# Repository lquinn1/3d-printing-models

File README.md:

# 3D Printing Models

A collection of 3D printable models — source files, print-ready files, and print settings for each.

## Model Index

<!-- The section between the markers below is generated by scripts/build_index.py. Don't edit it by hand. -->
<!-- INDEX:START -->
**7 models**

### Electrical

| | Model | Description | Material | Status | Tags |
|---|-------|-------------|----------|--------|------|
|  | [Homeline Load Center Filler Plate](models/homeline-filler-plate/README.md) | Snap-in filler plates (1- and 2-pole) for empty breaker openings in a Square D Homeline panel cover. Inspired by the HOMFPCP. | PLA (tested); ABS / ASA / PC recommended | Working | `electrical` `load-center` `breaker-panel` `filler-plate` `square-d` `homeline` `snap-fit` |

### Kitchen & BBQ

| | Model | Description | Material | Status | Tags |
|---|-------|-------------|----------|--------|------|
|  | [BBQ Probe Spool Stand](models/bbq-probe-spool-stand/README.md) | Stand for rotary BBQ probe spools, with front clips for the probe tips and a storage box with two pockets (V3). | ABS | Working | `bbq` `thermometer` `probe` `organizer` `storage` `inkbird` `alpha-grillers` |

### Lighting

| | Model | Description | Material | Status | Tags |
|---|-------|-------------|----------|--------|------|
|  | [Dragon Egg Nightlight](models/dragon-egg-nightlight/README.md) | Scaled dragon-egg lamp shade with an engraved base and a press-fit E26 socket deck, about 264 mm tall assembled. | PLA egg / ABS base and deck | Working | `nightlight` `lamp` `nursery` `dragon-egg` `e26` |

### Multiboard

| | Model | Description | Material | Status | Tags |
|---|-------|-------------|----------|--------|------|
|  | [Multiboard LED Light Bar](models/multiboard-led-light-bar/README.md) | One wedge bracket that holds an 18 x 8.5 mm LED channel on a Multiboard, aimed down the wall at 30°. The channel passes through, so use as many as you need, anywhere along the bar. | PLA (tested), PETG or ABS | Working | `multiboard` `led` `light-bar` `wall-wash` `push-fit` `honeycomb` |

### Organization

| | Model | Description | Material | Status | Tags |
|---|-------|-------------|----------|--------|------|
|  | [Example Cable Clip](models/example-cable-clip/README.md) | Placeholder model showing the README format. Delete once you add real models. | PETG | Example | `example` `cable-management` |
|  | [Remote Control Wall Holder](models/remote-wall-holder/README.md) | Slide-in wall cradle for a slim 151 x 38 x 13 mm LED-light remote. Screws to the wall; the remote lifts straight up and out. | PLA or PETG | Working | `remote` `wall-mount` `holder` `slide-in` `led-remote` `drywall` |

### Storage

| | Model | Description | Material | Status | Tags |
|---|-------|-------------|----------|--------|------|
|  | [Filament Dry Cabinet](models/filament-dry-cabinet/README.md) | Modular, stackable, heated and desiccant-dried 12-spool cabinet (one per material). ESPHome control, SK6812 lighting, closable PTFE ports and Spoolman slot IDs. Under 20 in deep and tall. | ABS / ASA | Design | `filament` `dry-box` `dehumidifier` `esphome` `esp32` `sk6812` `spoolman` `openprinttag` `nfc` `dowel` `modular` `stackable` `ptfe` |
<!-- INDEX:END -->

## Repository Layout

```
models/
  _template/            # copy this to start a new model
  <model-name>/
    README.md           # description, print settings, BOM, notes
    files/              # STL, 3MF, STEP, F3D, SCAD, etc.
    images/             # preview.png and build photos
scripts/
  build_index.py        # regenerates the index above
```

## Adding a Model

1. Copy `models/_template` to `models/<model-name>` (lowercase, hyphens, e.g. `spool-holder`).
2. Fill in the front matter at the top of the new `README.md` (`title`, `category`, `summary`, `material`, `status`, `tags`, and optionally `thumbnail`: the picture shown in the index; without it the first image in the README is used) and the rest of the page.
3. Put printable/source files in `files/` and a `preview.png` in `images/`.
4. Commit and push. The GitHub Action rebuilds the index automatically. To rebuild locally instead, run:

   ```
   python3 scripts/build_index.py
   ```

**Status values** (suggested): `Draft`, `Testing`, `Working`, `Final`, `Deprecated`.

## License

Unless a model folder has its own `LICENSE.md`:

- **Models and docs** (STL/STEP/3MF, READMEs, drawings, photos): [CC BY-NC-SA 4.0](https://creativecommons.org/licenses/by-nc-sa/4.0/). Free to print, modify and share with credit, **no commercial use**, and remixes keep the same license.
- **Code** (scripts in each model's `source/` or `cad/` folder, and `scripts/`): **MIT**.

Models with their own license:
- **BBQ Probe Spool Stand:** CC BY-SA 4.0, as required by the original it remixes (commercial use allowed with credit).
- **Filament Dry Cabinet:** same split as the default, with its vendor reference files excluded.

See [`LICENSE`](LICENSE).

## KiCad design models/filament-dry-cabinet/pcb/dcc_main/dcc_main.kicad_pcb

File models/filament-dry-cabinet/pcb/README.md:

# Cabinet electronics: two PCBs

Replaces the Perma-Proto protoboard. Everything is through-hole, so it can all be hand-soldered.

| Board | Size | Where | What's on it |
|---|---|---|---|
| **DCC-MAIN** (`dcc_main/`) | 170 × 60 mm, 2 layers, **2 oz copper** | Rear pod, on `carrier_main` (4 × M3, 160 × 50 mm: on the carrier's 10 mm grid) | ESP32-S3-DevKitC-1 in sockets, 10 A blade fuse, heater relay (G5LE) + MOSFET, fan driver with tach input and its own 0.5 A PTC fuse, 5 V distribution with a 3 A PTC for the LEDs, I²C pull-ups, NTC divider, door-reed input, ribbon header |
| **DCC-FRONT** (`dcc_front/`) | 80 × 44 mm, 2 layers, 1 oz | Header bay back plate, between the display and the encoder (x 335–415), over the cable slot | Ribbon header, display / NFC / encoder headers, 74AHCT125 LED level shifter with 330 Ω and 1000 µF at the strip, encoder pull-ups and filters, door-reed terminal |

Schematic: [`schematic.pdf`](schematic.pdf) (also [`../images/pcb_schematic.png`](../images/pcb_schematic.png)).

Wiring between the boards and everything else: [`../wiring/wire_list.csv`](../wiring/wire_list.csv) and DESIGN.md §19.

## Ordering

Upload `dcc_main/dcc_main_gerbers.zip` and `dcc_front/dcc_front_gerbers.zip` as they are (Gerber + Excellon, KiCad names). Use the house defaults (1.6 mm FR-4, HASL or ENIG, any colour), but **order the controller with 2 oz outer copper**: the heater's 6.3 A runs through it on 2 mm tracks and both ground pours. Parts per board: `dcc_*_bom.csv`. They're also in the cabinet BOM.

## How the heater is switched

`+24V → F1 (10 A) → K1 relay contact → J2 heater (with the 102 °C TCO in its lead) → Q1 MOSFET → GND`

- **Q1 (GPIO45)** does the PWM (about a 5 s period in ESPHome `slow_pwm`).
- **K1** is the safety switch. Its coil is fed through the **KSD301 (J3)**, so at 85 °C the thermostat drops the relay whatever the firmware does. Q2 (GPIO46) lets the firmware drop it too, for the interlocks.
- **GPIO45 and GPIO46 are ESP32-S3 boot-strap pins.** Each has a 10 kΩ pull-down (R4, R2), which keeps it low at reset, as the chip needs. It also means the heater and relay are off while the board boots.

## Pin map and ribbon

The ESP32 pin map and the 26-way ribbon pinout are on the last two pages of the schematic, and in [`circuit.py`](circuit.py), which is the source for both boards.

- **Not used:** GPIO35–37 (octal PSRAM on the N16R8 module), GPIO19/20 (USB), GPIO43/44 (log UART), GPIO0 (BOOT), GPIO38/48 (the DevKit's RGB LED).
- **Fan PWM is inverted.** Q3 is an open collector, so set `inverted: true` on the ESPHome output. At boot Q3 is off, so the fan runs at full speed until the firmware takes over, which is the safe way round.
- **Ribbon:** in the flat cable, SCK, MOSI, MISO and the LED data line each sit next to a ground wire. Keep SPI at 10 MHz or less.

## DevKit header spacing

Espressif's drawing puts the two pin rows 22.86 mm apart, but some boards measure 25.4 mm. U1B has a **second row of holes 2.54 mm further out**, wired in parallel. Measure your board and solder the J3 socket into whichever row fits; leave the other row empty.

## Checks (run on every build)

- **DRC: 0 errors, 0 unconnected pads** on both boards. Reports: `dcc_*_drc.txt`. The only warnings left are silkscreen labels touching outlines.
- **Every pad's net matches `circuit.py`.**
- **Track widths:** heater and 24 V nets are 2.0 mm, 5 V nets 1.0 mm, signals 0.4 mm. Clearance is 0.2 mm (0.3 mm on the 24 V nets).
- **Copper keep-outs:** none under the DevKit's antenna, and none within 0.8 mm of the board edge.
- **Schematic cross-check:** all 43 parts drawn in the schematic are on the boards with the same values, and vice versa.

## Rebuild

```
python3 pcb/build.py        # place, autoroute, pour ground, DRC, Gerbers + drill, per-board BOM
python3 pcb/schematic.py    # schematic.pdf and images/pcb_schematic.png
```

You need KiCad 7 (`kicad-cli` and the `pcbnew` Python module), Java, `freerouting.jar` v1.9 (set `FREEROUTING` to its path), and `xvfb-run`. Placement lives in `circuit.py`: move a part there, rerun, and the router lays the tracks again. The `.kicad_pcb` files open in KiCad 7 or later if you'd rather edit the layout by hand.

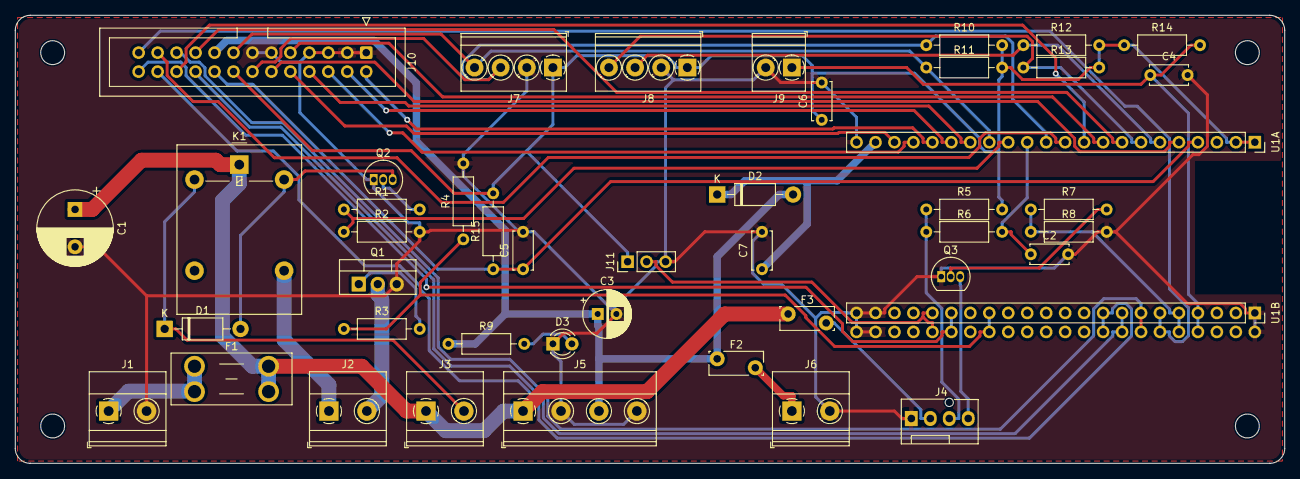
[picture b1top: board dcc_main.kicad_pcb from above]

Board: 2 copper layers, 170.0 x 60.0 mm, 49 parts (0 on the bottom side), 44 nets.

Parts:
C1: 100uF 35V; CP_Radial_D10.0mm_P5.00mm
C2: 10nF; C_Disc_D5.0mm_W2.5mm_P5.00mm
C3: 100uF 10V; CP_Radial_D6.3mm_P2.50mm
C4, C5, C6, C7: 100nF; C_Disc_D5.0mm_W2.5mm_P5.00mm
D1: 1N4007; D_DO-41_SOD81_P10.16mm_Horizontal
D2: 1N5819; D_DO-41_SOD81_P10.16mm_Horizontal
D3: PWR; LED_D3.0mm
F1: 10 A mini blade; Fuseholder_Blade_Mini_Keystone_3568
F2: 3A PTC; Fuse_Bourns_MF-RG300
F3: 0.5A PTC; Fuse_Bourns_MF-RG300
H1, H2, H3, H4: MountingHole_3.2mm_M3
J1: 24 V IN; TerminalBlock_Phoenix_MKDS-1,5-2-5.08_1x02_P5.08mm_Horizont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
J2: HEATER; TerminalBlock_Phoenix_MKDS-1,5-2-5.08_1x02_P5.08mm_Horizont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
J3: KSD301; TerminalBlock_Phoenix_MKDS-1,5-2-5.08_1x02_P5.08mm_Horizont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
J4: FAN 24V PWM; FanPinHeader_1x04_P2.54mm_Vertical
J5: BUCK 24V/5V; TerminalBlock_Phoenix_MKDS-1,5-4-5.08_1x04_P5.08mm_Horizont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
J6: LED 5V OUT; TerminalBlock_Phoenix_MKDS-1,5-2-5.08_1x02_P5.08mm_Horizont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
J7: SHT45 CHAMBER; TerminalBlock_Phoenix_PT-1,5-4-3.5-H_1x04_P3.50mm_Horizontal
J8: SHT40 PLENUM; TerminalBlock_Phoenix_PT-1,5-4-3.5-H_1x04_P3.50mm_Horizontal
J9: NTC; TerminalBlock_Phoenix_PT-1,5-2-3.5-H_1x02_P3.50mm_Horizontal
J10: FRONT 2x13; IDC-Header_2x13_P2.54mm_Vertical
J11: SPARE IO21; PinHeader_1x03_P2.54mm_Vertical
K1: G5LE-1A4 DC24; Relay_SPDT_Omron-G5LE-1
Q1: IRLB3034; TO-220-3_Vertical
Q2, Q3: 2N3904; TO-92_Inline
R1, R7: 4k7; R_Axial_DIN0207_L6.3mm_D2.5mm_P10.16mm_Horizontal
R2, R4, R5, R8, R15: 10k; R_Axial_DIN0207_L6.3mm_D2.5mm_P10.16mm_Horizontal
R3: 100R; R_Axial_DIN0207_L6.3mm_D2.5mm_P10.16mm_Horizontal
R6, R9: 1k; R_Axial_DIN0207_L6.3mm_D2.5mm_P10.16mm_Horizontal
R10, R11, R12, R13: 2k2; R_Axial_DIN0207_L6.3mm_D2.5mm_P10.16mm_Horizontal
R14: 10k 1%; R_Axial_DIN0207_L6.3mm_D2.5mm_P10.16mm_Horizontal
U1A: ESP32 J1; PinSocket_1x22_P2.54mm_Vertical
U1B: ESP32 J3; PinSocket_1x22_P2.54mm_TwinRow

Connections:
+3V3: C6.1, J7.1, J8.1, J10.16, J11.1, R5.2, R10.2, R11.2, R12.2, R13.2, R14.1, R15.2, U1A.1, U1A.2
+5V: C3.1, D2.2, F2.1, J5.3, J10.17, R9.1
+24V: C1.1, F1.2, F3.1, J3.1, J5.1, K1.1
+24V_IN: F1.1, J1.1
COIL_LO: D1.2, K1.5, Q2.3
CTP_INT: J10.21, U1B.7
ENC_A: J10.24, U1B.9
ENC_B: J10.25, U1B.6
ENC_SW: J10.26, U1B.17
ESP_5V: C7.1, D2.1, U1A.21
FAN_24V: F3.2, J4.2
FAN_OC: J4.4, Q3.3
FAN_PWM: R7.1, R8.1, U1B.5
FAN_TACH: C2.1, R6.2, U1A.13
FRONT_RST: J10.20, U1B.8
GND: C1.2, C2.2, C3.2, C4.2, C5.2, C6.2, C7.2, D3.1, J1.2, J4.1, J5.2, J5.4, J6.2, J7.2, J8.2, J9.2, J10.1, J10.3, J10.5, J10.7, J10.11, J10.13, J11.3, Q1.3, Q2.1, Q3.1, R2.2, R4.2, R8.2, U1A.22, U1B.1, U1B.21, U1B.22
HTR_N: J2.2, Q1.2
HTR_P: J2.1, K1.4
HTR_PWM: R3.1, R4.1, U1B.15
LED_5V: F2.2, J6.1
LED_A: D3.2, R9.2
LED_DIN: J10.12, U1A.5
MISO: J10.6, U1A.19
MOSI: J10.4, U1A.17
NFC_BUSY: J10.22, U1A.10
NFC_NSS: J10.9, U1A.9
NFC_RST: J10.23, U1A.11
NTC: C4.1, J9.1, R14.2, U1B.4
Q1_G: Q1.1, R3.2
Q2_B: Q2.2, R1.2
Q3_B: Q3.2, R7.2
REED: C5.1, J10.18, R15.1, U1A.4
RELAY_EN: R1.1, R2.1, U1A.14
SCK: J10.2, U1A.18
SCL_A: J7.4, J10.15, R11.1, U1A.15
SCL_B: J8.4, R13.1, U1A.7
SDA_A: J7.3, J10.14, R10.1, U1A.12
SDA_B: J8.3, R12.1, U1A.6
SPARE_IO21: J11.2, U1B.18
TACH_RAW: J4.3, R5.1, R6.1
TFT_BL: J10.19, U1A.8
TFT_CS: J10.8, U1A.16
TFT_DC: J10.10, U1A.20
TSTAT_OUT: D1.1, J3.2, K1.2

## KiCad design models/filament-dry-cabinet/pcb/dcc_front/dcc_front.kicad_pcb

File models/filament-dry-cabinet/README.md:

---
title: Filament Dry Cabinet
category: Storage
status: Design
material: ABS / ASA
printer: Voron 2.4 R2 350
tags: [filament, dry-box, dehumidifier, esphome, esp32, sk6812, spoolman, openprinttag, nfc, dowel, modular, stackable, ptfe]
thumbnail: images/thumbnail.jpg
summary: Modular, stackable, heated and desiccant-dried 12-spool cabinet (one per material). ESPHome control, SK6812 lighting, closable PTFE ports and Spoolman slot IDs. Under 20 in deep and tall.
---

# Filament Dry Cabinet

A modular cabinet that stores **12 × 1 kg spools** and keeps them dry. A low-voltage **PTC heater** circulates warm air through **pull-out silica gel cartridges**. An **ESP32 running ESPHome** controls it, with a local display and knob for setpoints, and integrates with Home Assistant. **SK6812** lighting can highlight individual slots. Each spool position has an ID (`PETG-F3`, for example) for Spoolman's Location field. You'll build **one cabinet per material**. It plugs in through an **IEC C14 fused inlet** (120 V). At **19.4 in deep and 19.4 in tall**, it fits standard 20 in shelves. Cabinets **stack**, and **closable PTFE ports** on the top and back can feed a printer straight from any slot.

**Status: CAD, PCBs and firmware done; ready for the test build.** The shell (§13), front frame and header (§14), door (§15), rear pod (§16), interior drying unit (§17) and fit-test coupons (§12); two custom PCBs (§18), wiring (§19) and the ESPHome firmware (`firmware/`). The as-built parts list is in **[BOM.md](BOM.md)** (about $1,018 for one cabinet). The PN5180 NFC component is next. See **[DESIGN.md](DESIGN.md)** for the full spec.

*The top picture is a Blender/Cycles render of the CAD (`source/render/photo/`); the printer in it is a simplified stand-in. The others are rendered straight from the CAD (`cad/render_hero.py`).*

## At a Glance

| | |
|---|---|
| Capacity | 12 spools: two rows of 6, with the back row raised 120 mm |
| Size | 531 W × 442 D (492 with rear control pod) × 494 H mm (20.9 × 17.4 / 19.4 × 19.4 in) |
| Shelves | 1 in poplar dowel rods (same in every cabinet) in printed cradles, with printed index collars every 80 mm |
| Shell | Printed ABS/ASA tile panels (≤ 330 mm) with 1/2 in XPS foam, and a twin-pane polycarbonate door |
| PTFE ports | 12 on top (one per slot) + 12 on the back. Each one takes a PTFE pass-through module (PC4-M10) or a sealed blank plug. |
| Stacking | Feet nest into pockets in the cabinet below, with optional side links. Stacks of 2–3. |
| Drying | 24 V PTC heater, 150 W in every cabinet with PID (autotune), + PWM fan + about 700 g of silica gel |
| Control | ESP32-S3, SHT45/SHT40, 3.5 in IPS capacitive touchscreen TFT, 480 × 320 (shows the label; touch firmware later) + encoder, ESPHome |
| NFC | **PN5180 tap pad** in the header for **OpenPrintTag** (ISO 15693) and NTAG tags. Tap a spool and pick a slot, and Spoolman's Location updates. |
| Power | 120 V IEC C14 fused and switched inlet → Mean Well 24 V PSU in a rear pod outside the chamber |
| Door | Twin-pane polycarbonate, soft neoprene seal, flush lift-bar handle that is also a draw-in latch |
| Safety | Hardware thermal cutouts (85 °C auto-reset on a heater relay + 102 °C fuse) and firmware interlocks |

## Files

| File | Description |
|------|-------------|
| [`firmware/`](firmware/README.md) | ESPHome firmware for one cabinet (`dry-cabinet.yaml`), with flashing steps, first power-up checks and how the control works |
| [`pcb/`](pcb/README.md) | Electronics: two KiCad PCBs (controller + front breakout) built from `circuit.py`, with Gerbers, schematic and per-board BOMs |
| [`cad/`](cad/) | Parametric CAD: `params.py` (all dimensions), `coupons.py` (fit-test parts), `tiles.py` (20 shell tiles, feet, cradles), `front.py` (frame, header, LED rails), `door.py` (door, hinges, lift-bar latch, tag), `render_latch.py` (latch renders and animation), `latch_coupon.py` (latch fit-test coupon), `pod.py` (rear pod), `interior.py` (desiccant, plenum, heater and floor ducts, sensor housings), `verify*.py` (assembly and swing checks), `preview.py` / `render_tiles.py` (images); STLs in `cad/stl/` |
| [`DESIGN.md`](DESIGN.md) | Full design spec: requirements, layout options, construction, drying, electronics, ESPHome entities, Spoolman scheme, parts list, open questions |
| [`BOM.md`](BOM.md), [`BOM.csv`](BOM.csv) | As-built bill of materials: links, prices, quantities, where each part is used, status and test results. Generated from `bom/bom_source.csv` by `bom/build_bom.py` |
| [`QA_REVIEW.md`](QA_REVIEW.md) | Design and CAD QA review: what was fixed, and prioritised recommendations |
| [`images/render_front.jpg`](images/render_front.jpg), [`render_stack.jpg`](images/render_stack.jpg), [`render_rear.jpg`](images/render_rear.jpg) | Concept renders (front, stacked pair, rear) |
| [`images/wiring.png`](images/wiring.png) | Electrical block diagram |
| [`source/layout.py`](source/layout.py) | Layout calculator. Change the spool and rod sizes or the offset and rerun it. |
| [`source/draw.py`](source/draw.py), [`source/wiring.py`](source/wiring.py) | Scripts that draw the layout and wiring figures |
| [`source/render/`](source/render/) | The software renderer (`scene.py`) used by every `cad/render_*.py`. The three presentation views (front, rear, stack) come from `cad/render_hero.py`, built from the real CAD parts |

## License

- **Design files and docs** (STL/STEP, DESIGN.md, drawings, renders): [CC BY-NC-SA 4.0](https://creativecommons.org/licenses/by-nc-sa/4.0/). Free to build, modify and share with credit, but **no commercial use**, and remixes keep the same license.
- **Code** (Python in `cad/`, `source/` and `bom/`, and the ESPHome YAML and components when they're added): **MIT**.
- The display vendor's drawing and pinout in `docs/`, and `images/concept.jpg`, aren't covered.

See [`LICENSE.md`](LICENSE.md).

## Revision History

- **v0.25** (2026-11-25): **fit-test round 2.** `tile_joint_b` confirmed (0.05 mm flank gap). Port thread clearance **0.35 mm** (was 0.25), tested with **wall order inner/outer** (now in the print settings): the seven socket tiles, plug, PTFE module and gland regenerated. O-ring groove ID **23.0** (was 22.6) so the ring holds on better, plus a new `oring_groove_coupon` (22.6 / 23.0 / 23.4) to confirm it.
- **v0.24** (2026-11-25): **bottom LED strip.** Two new printed rails (`led_rail_bottom_left/right`) on the floor behind the door sill, flush with it, carry 23 more SK6812 LEDs aimed up and back at the spools, with a gap at slot 3 for the floor duct. One data chain of 51 LEDs: the top strip (data in at the right) feeds the bottom one through a wire down the front-left corner (W26, W27). Firmware: per-slot lights cover both strips, plus a **2.0 A LED current cap** so the 3 A 5 V supply is never overloaded. Inserts in the bottom rail; wiring, BOM quantities and renders updated (total unchanged, about $1,018).
- **v0.23.1** (2026-11-25): **photoreal render** of two cabinets on a wire shelf next to a Voron 2.4-style printer ([`images/render_photo_shelf.jpg`](images/render_photo_shelf.jpg)), Blender/Cycles from the CAD (`source/render/photo/`).
- **v0.23** (2026-11-25): **5 V supply is now a Mean Well SD-15B-5** ($14.80, 18–36 V in, 5 V 3 A, protected) in place of the $39.95 Pololu D36V50F5; it sits on `carrier_left` between printed corner stops (checked against the cover, PSU and glands). 5 V budget worked out: about 2 A worst real case. **Controller is now the ESP32-S3-DevKitC-1-N16R8** (16 MB flash; same pinout), firmware set to 16 MB and recompiled. Wiring list, schematic and pod render updated. About $1,018.
- **v0.22** (2026-11-25): **1 in poplar dowels replace the PVC rods** (Madison Mill 436580, two 48 in dowels per cabinet). One rod type for every plastic, and about 0.3 mm sag loaded against 2 mm or more for PVC at 50 °C, so the CPVC line for hot cabinets is gone. Rod cradles and collars resized for 25.4 mm (collar grip raised for undersize dowels); the cabinet size is unchanged. New prep steps: pre-dry, seal and measure the dowels (§4.3). BOM about $1,043.
- **v0.21** (2026-11-25): the NFC tap zone is now a **64 × 46 mm rectangle with a phone-and-waves icon and TAP HERE**, and the encoder gets a **printed orange knob** (`encoder_knob`, D-bore for the 6 mm shaft) in place of the aluminium one. Renders and the front layout drawing updated. About $1,026.
- **v0.20** (2026-11-25): **orange accents.** New `tft_bezel` (orange frame round the screen) and `nfc_tap_overlay` (orange Ø46 tap zone over the NFC reader), glued on the fascia and located by pegs. The fascia's old debossed NFC ring and its window chamfer are replaced by them. The latch handle, port plugs, PTFE modules and cable glands are printed in orange too. BOM: a 1 kg spool of orange ABS/ASA for the accents (about $1,029). Renders updated.
- **v0.19.1** (2026-11-25): **all renders redone from the current CAD.** The front, rear and stacked presentation views were still the v0.6 concept model (NFC box on the face, side handle, old door); they now come from `cad/render_hero.py` using the real tiles, frame, door with the lift-bar, pod, glands, interior and spools, with the screen showing the firmware's label page. Every `cad_*` render, the layout drawings (seal, latch, screen, 494 mm height), the schematic and the wiring diagram were re-run.
- **v0.19** (2026-11-25): **ESPHome firmware** in `firmware/`: sensors, PID heater with saved autotune, Maintain / Dry / Off modes, all firmware interlocks, fan control, door pause, label and detail screens, the encoder menu, light colours, find-slot (also as an HA action), desiccant tracking. Compiles on ESPHome 2026.11. NFC and touch come later.
- **v0.18** (2026-11-25): **Custom PCBs** replace the protoboard. The controller board (rear pod) carries a socketed ESP32-S3 DevKitC-1, the relay and MOSFET heater stage, the fan driver, fuses and sensor inputs. The front breakout (header bay) carries the display, NFC and encoder headers and the LED level shifter. A 26-way ribbon joins them. Files: KiCad boards, Gerbers, schematic and per-board BOMs in `pcb/`. **Wiring:** a full wiring diagram and a 25-wire list (gauge, colour, length, route). A **second cable gland** (14th back socket) for the ribbon, and a 40 × 7 mm slot into the header bay in place of the Ø10 hole. Also a **latch fit-test coupon**. BOM: every board part and harness item on its own line; the ESP32 is now the official Espressif DevKitC-1-N8R8. About $1,006.
- **v0.17** (2026-11-24): **Flush lift-bar latch** replaces the side lever. The handle is a bar flush in the right door stile; pull its bottom end and a hidden hook drops off a steel pin in the frame stile, then the door opens. Push the door shut and it latches itself; press the bar flush and it draws the door up to 2 mm onto the seal. Nothing sticks out past the door. Renders: closed, pulled, hidden parts, a 5-step section and an animation. BOM: post, sleeve, insert, washer and M3 × 12 removed; M3 × 25 and M3 × 16 flat heads added. About $931.
- **v0.16** (2026-11-24): QA fixes in the CAD and a fully broken-out BOM. **Door:** printed **draw latch** after the Clicky-Clack door (lever on the door edge, post on the frame stile, ramp draws the door in about 2 mm, magnetic click), D-pull handle removed; seal changed to 5 × 3 mm soft neoprene at 33 % squeeze (was EPDM at 50 %); one-piece hinge frame leaves, knuckles Ø11. **Interior:** PTFE pads under the heater; heater relay so the KSD301 switches a coil, not 6 A DC. **Tiles:** name debossed on each tile, 3 mm chamfered outside corners, foot base band. LED rail knife edges clipped. **BOM:** 71 lines, each part and passive on its own line, a protoboard for the electronics, an alternate source and link for every part, no auction sites. About $936. HP05-1/22 heater dropped (wrong part); a generic finned PTC is listed until a heater with a known surface temperature is confirmed.
- **v0.15.1** (2026-11-24): design and CAD **QA review** ([`QA_REVIEW.md`](QA_REVIEW.md)). Fixed: 11 threaded STLs had non-manifold (pinched) edges, now all 66 STLs are watertight when welded and `save()` checks for it; the desiccant lid was exported upside down. BOM: 12 PC4-M10 couplers, not 24 ($781). Open recommendations: lower-temperature PTC and a relay for the KSD301, test the door seal force, one-piece hinge leaves, CPVC rods for 55–60 °C cabinets, part labels on the tiles.
- **v0.15** (2026-11-24): as-built **bill of materials** for the first test build: [`BOM.md`](BOM.md) / [`BOM.csv`](BOM.csv), 42 lines with links, prices, quantities from the CAD, where each part is used, and status and test columns. About $793 for one cabinet. Filament estimate raised to 7 kg (from the STL volumes). DESIGN §9 now points to it.
- **v0.14** (2026-11-24): CAD phase 6, the interior: two lift-out desiccant cartridges (645 cm³ each) under back slots 1 and 6, a plenum with the 80 mm fan, a stepped heater duct (KSD301, TCO, NTC), a floor duct to the door, and sensor housings. **Correction:** a back spool comes out only after the front spool in its slot is removed (the earlier spec said it could go over the front spool). Removal paths are simulated in CAD. The 85 mm of headroom is kept, and the cabinet stays 19.4 in tall.
- **v0.13** (2026-11-24): CAD phase 5, the rear control pod. It's 330 × 230 × 50 mm: LRS-200-24 on rails with clamp bars, a snap-in IEC inlet in the side wall, two drillable carrier plates, a vented cover with the mains warning, and a gland module in the 13th back socket. The pod inserts in the back tiles moved to suit it. The header cable now runs through the chamber to the gland (header pass-through enlarged to Ø10). All assembly checks re-run clean. Details in DESIGN §16.
- **v0.12** (2026-11-24): CAD phase 4, the door. 30 mm members with twin polycarbonate panes (488.4 × 372.5 mm each) in grooves, rails in halves with a welded tenon, printed hinges with M3 pins, 4 magnets (catch + reed), D-pull, slot numbers 1–6 and the backup tag. Swing checked clear to 110°, and the seal loop is fully backed. Details in DESIGN §15.
- **v0.11** (2026-11-24): CAD phase 3, the front frame and header. The frame ring is two stiles, a split bottom rail and the header lip, with hinge inserts, magnet and reed pockets and a reed wire channel. The header is 3 chassis pieces and 3 fascias (NFC pad, 3.5 in TFT bezel with standoffs, encoder), plus 2 LED rails inside. The door opening is 480 × 377.8 mm. Verified against the shell. Parts, hardware and print notes are in DESIGN §14.
- **v0.10.1** (2026-11-24): O-ring groove on the port modules tightened (22.6 ID × 2.5 wide, was 22.0 × 2.7) after the test ring sat loose. The ring now stretches onto the groove's inner wall.
- **v0.10** (2026-11-23): CAD phase 2, the full shell: 20 tiles (all ≤ 299 × 226 mm) with port sockets, stacking pockets, cradle, pod and foot inserts, plus 4 feet and 8 rod cradles. Top and bottom span the full width so the walls carry the load. Assembly verified in CAD (no overlaps, every bolt station clear, rods and stacking fit). Parts list, hardware, foam sizes and assembly order are in DESIGN §13.
- **v0.9.2** (2026-11-23): first fit-test results in ABS: port socket clearance 0.25 mm chosen, tile groove fixed to an even 0.05 mm offset of the V tongue (reprint `tile_joint_b` to confirm), foam (0.5 in) and PVC (1.05 in OD) confirmed.
- **v0.9.1** (2026-11-22): display chosen: **3.5 in IPS 480 × 320 SPI TFT with FT6336U capacitive touch** (Haldzemo, 98 × 55.5 mm board). It still fits the 68 mm header. Mounting, bezel window, pinout and wiring notes are in DESIGN §6.6, and the vendor drawing and pinout are in `docs/`.
- **v0.9** (2026-11-22): display changed to a **3.2 in IPS capacitive touch TFT** (FT6336U boards are mostly 3.2 in). The header grows from 60 to 68 mm to fit it, so the cabinet is 494 mm (19.4 in) tall, 484 mm per cabinet when stacked. Figures and renders updated.
- **v0.8.1** (2026-11-22): the BOM uses the **capacitive touchscreen** version of the 2.8 in display (FT6336U on I2C, INT/RST pins reserved) so touch can be added in firmware later. The rotary encoder stays.
- **v0.8** (2026-11-22): the printed label plate is replaced by a **2.8 in IPS TFT that shows the material name** on a colour band, with status below. Added cabinet name, label colour and idle brightness settings, the screen behaviour, a backup tag on the door rail, and updated the header layout, figures and renders.
- **v0.7** (2026-11-22): CAD phase 1, fit-test coupons for the port thread and O-ring, PC4-M10 hole, rod cradle, index collar, tile joint, inserts and foam pocket. Walls are now 15.7 mm (2.4 mm skin + 1/2 in foam), so the outside is 531 × 442 (492) × 485 mm. The O-ring is now 22 × 2 mm. Index collars now slide on from the rod end.
- **v0.6.1** (2026-11-22): added concept renders (front, stacked PLA + PETG pair, rear). No spec changes.
- **v0.6** (2026-11-22): added an OpenPrintTag NFC reader: a PN5180 tap pad in the header, a Spools menu for checking spools in and out, an HA → Spoolman flow, and the ESPHome PN5180 component as new firmware work.
- **v0.5** (2026-11-22): RGB colour options for the lights: a preset colour list and a custom RGB colour, set from the encoder menu or Home Assistant.
- **v0.4** (2026-11-22): PID autotune now starts from the encoder menu (Tuning → PID autotune), with a confirmation step, instead of a button. Added a draft menu layout.
- **v0.3** (2026-11-22): every cabinet uses the same parts: a 150 W heater and Mean Well LRS-200-24, with PID control and autotune for each cabinet.
- **v0.2** (2026-11-22): decisions added: 20 in shelves (cabinet 19.5 in tall, lift room kept), closable PTFE ports on the top and back, stacking, 2.0 in TFT, 120 V only, ABS/ASA shell.
- **v0.1** (2026-11-22): first design spec and layout for review.

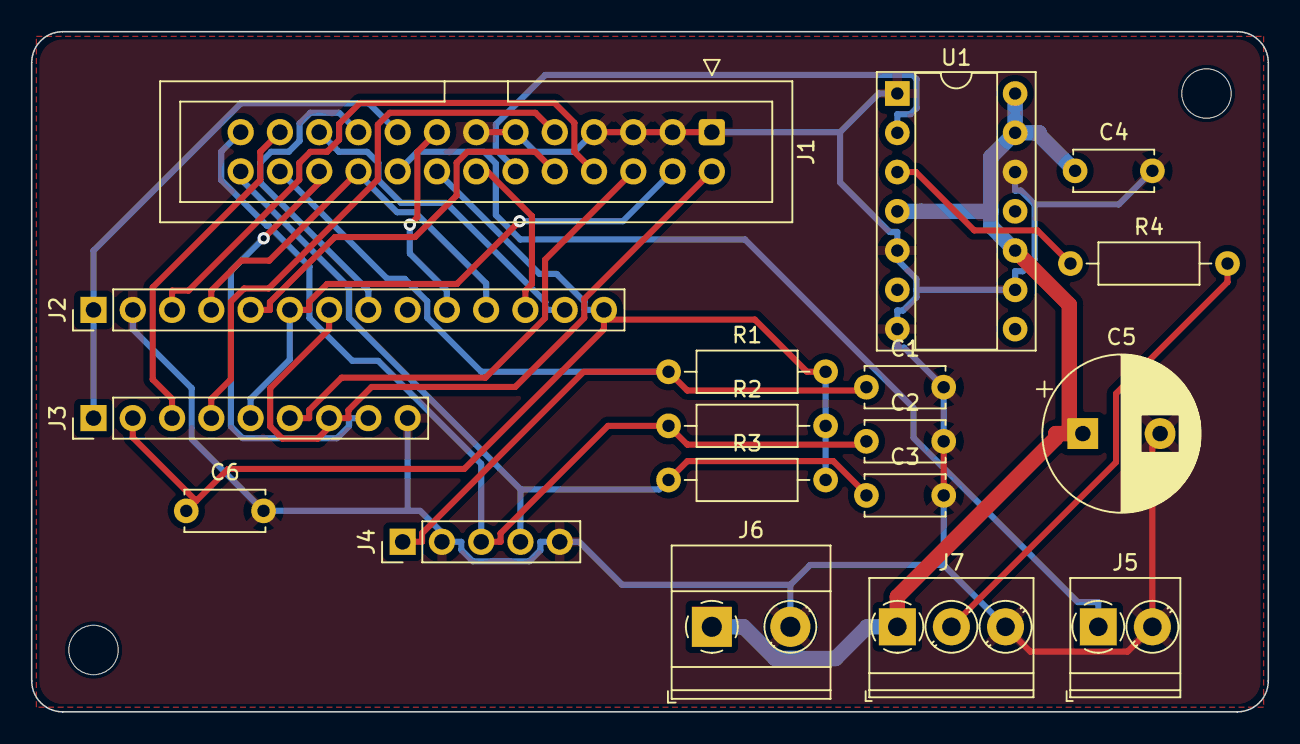
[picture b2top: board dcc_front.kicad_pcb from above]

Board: 2 copper layers, 80.0 x 44.0 mm, 20 parts (0 on the bottom side), 24 nets.

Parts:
C1, C2, C3: 10nF; C_Disc_D5.0mm_W2.5mm_P5.00mm
C4, C6: 100nF; C_Disc_D5.0mm_W2.5mm_P5.00mm
C5: 1000uF 16V; CP_Radial_D10.0mm_P5.00mm
H1, H2: MountingHole_3.2mm_M3
J1: FROM POD 2x13; IDC-Header_2x13_P2.54mm_Vertical
J2: TFT 3.5in; PinHeader_1x14_P2.54mm_Vertical
J3: PN5180; PinHeader_1x09_P2.54mm_Vertical
J4: ENCODER; PinHeader_1x05_P2.54mm_Vertical
J5: REED; TerminalBlock_Phoenix_PT-1,5-2-3.5-H_1x02_P3.50mm_Horizontal
J6: LED 5V IN; TerminalBlock_Phoenix_MKDS-1,5-2-5.08_1x02_P5.08mm_Horizont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
J7: LED STRIP; TerminalBlock_Phoenix_PT-1,5-3-3.5-H_1x03_P3.50mm_Horizontal
R1, R2, R3: 10k; R_Axial_DIN0207_L6.3mm_D2.5mm_P10.16mm_Horizontal
R4: 330R; R_Axial_DIN0207_L6.3mm_D2.5mm_P10.16mm_Horizontal
U1: 74AHCT125; DIP-14_W7.62mm_Socket

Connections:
+3V3: C6.1, J1.16, J2.14, J3.2, R1.2, R2.2, R3.2
+5V: J1.17, J2.1, J3.1
CTP_INT: J1.21, J2.13
ENC_A: C1.1, J1.24, J4.1, R1.1
ENC_B: C2.1, J1.25, J4.3, R2.1
ENC_SW: C3.1, J1.26, J4.4, R3.1
FRONT_RST: J1.20, J2.4, J2.11
GND: C1.2, C2.2, C3.2, C4.2, C5.2, C6.2, J1.1, J1.3, J1.5, J1.7, J1.11, J1.13, J2.2, J3.9, J4.2, J4.5, J5.2, J6.2, J7.3, U1.1, U1.5, U1.7, U1.9, U1.12
LED_5V: C4.1, C5.1, J6.1, J7.1, U1.4, U1.10, U1.13, U1.14
LED_DIN: J1.12, U1.2
LED_DO: J7.2, R4.2
LED_Y: R4.1, U1.3
MISO: J1.6, J3.6
MOSI: J1.4, J2.6, J3.5
NFC_BUSY: J1.22, J3.8
NFC_NSS: J1.9, J3.4
NFC_RST: J1.23, J3.3
REED: J1.18, J5.1
SCK: J1.2, J2.7, J3.7
SCL_A: J1.15, J2.10
SDA_A: J1.14, J2.12
TFT_BL: J1.19, J2.8
TFT_CS: J1.8, J2.3
TFT_DC: J1.10, J2.5

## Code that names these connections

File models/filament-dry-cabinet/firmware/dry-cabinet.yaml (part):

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  led_limit_ma: "2000"                # firmware cap on the LED current, so the 3 A 5 V supply keeps 0.85 A for the rest

  # GPIO (pcb/circuit.py)
  pin_reed: GPIO4
  pin_led: GPIO5
  pin_sda_b: GPIO6
  pin_scl_b: GPIO7
  pin_sda_a: GPIO8
  pin_scl_a: GPIO9
  pin_tft_cs: GPIO10
  pin_mosi: GPIO11
  pin_sck: GPIO12
  pin_miso: GPIO13
  pin_tft_dc: GPIO14
  pin_tft_bl: GPIO15
  pin_nfc_nss: GPIO16
  pin_nfc_busy: GPIO17
  pin_nfc_rst: GPIO18
  pin_ntc: GPIO1
  pin_fan_pwm: GPIO2
  pin_fan_tach: GPIO3
  pin_enc_a: GPIO39
  pin_front_rst: GPIO40
  pin_ctp_int: GPIO41
  pin_enc_b: GPIO42
  pin_htr_pwm: GPIO45
  pin_relay: GPIO46
  pin_enc_sw: GPIO47

esphome:
  name: ${name}
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# ----------------------------------------------------------------------------- buses
i2c:
  - id: bus_a                 # chamber SHT45 + display touch (FT6336U, phase 6)
    sda: ${pin_sda_a}
    scl: ${pin_scl_a}
    frequency: 100kHz
  - id: bus_b                 # plenum SHT40 (same address as the SHT45, so its own bus)
    sda: ${pin_sda_b}
    scl: ${pin_scl_b}
    frequency: 100kHz

spi:
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  # heater outlet NTC: 3V3 -> R14 10k -> ADC -> NTC -> GND
  - platform: adc
    id: ntc_v
    pin: ${pin_ntc}
    attenuation: 12db
    update_interval: 5s
    internal: true
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    id: fan_rpm
    name: Fan speed
    pin:
      number: ${pin_fan_tach}
      ignore_strapping_warning: true   # JTAG-select strap, unused unless an eFuse is burned
    unit_of_measurement: RPM
    update_interval: 5s
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
  - platform: rotary_encoder
    id: knob
    pin_a: ${pin_enc_a}         # 10k pull-ups and 10 nF on the front board
    pin_b: ${pin_enc_b}
    resolution: 1
    internal: true
    on_clockwise:
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    id: door
    name: Door
    device_class: door
    pin: ${pin_reed}           # reed closed (door shut) pulls it low; R15 pulls it up
    filters:
      - delayed_on_off: 50ms
    on_press:
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  - platform: gpio
    id: enc_button
    pin:
      number: ${pin_enc_sw}
      inverted: true           # R3 on the front board pulls it up; pressing pulls it low
    filters:
      - delayed_on_off: 20ms
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  - platform: slow_pwm
    id: heater_pwm
    pin:
      number: ${pin_htr_pwm}
      ignore_strapping_warning: true   # R4 holds it low at reset, as the strap needs
    period: 5s
  - platform: ledc
    id: fan_pwm
    pin: ${pin_fan_pwm}
    frequency: 25000Hz
    inverted: true                     # Q3 is an open collector: on = PWM pin low
  - platform: ledc
    id: backlight_pwm
    pin: ${pin_tft_bl}
    frequency: 5000Hz
  # PID writes here; the control loop decides what actually reaches the heater
  - platform: template
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    id: tft
    model: ST7796
    spi_id: spi_bus
    cs_pin: ${pin_tft_cs}
    dc_pin: ${pin_tft_dc}
    reset_pin: ${pin_front_rst}       # shared with the touch controller's reset
    data_rate: 10MHz                  # 1.5 m ribbon: keep it at 10 MHz or less
    rotation: ${tft_rotation}
    invert_colors: ${tft_invert}
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
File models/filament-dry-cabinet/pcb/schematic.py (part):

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def b_heater_path(d):
    d += elm.Label().label('+24V', loc='left')
    d += elm.Switch().right().label(part(M, 'K1', 'G5LE-1A4 DC24') + '\ncontact COM-NO')
    d += elm.Line().right(1).label('HTR_P', loc='top')
    d += elm.ResistorVar().right().label('J2: PTC heater 24 V 150 W\nwith the TCO 102 °C in series\n(off board)', loc='bottom')
    d += elm.Line().right(1); d += elm.Label().label('HTR_N\n(Q1 drain)', loc='right')

def b_heater_fet(d):
    q = elm.NFet().reverse().label(part(M, 'Q1', 'IRLB3034'), loc='right'); d += q
    d += elm.Line().at(q.drain).up(0.5); d += elm.Label().label('HTR_N', loc='top')
    d += elm.Ground().at(q.source)
    d += elm.Line().at(q.gate).left(2.5); d += elm.Dot(); d.push()
    d += elm.Resistor().down().label(part(M, 'R4', '10k'), loc='bottom'); d += elm.Ground()
    d.pop(); d += elm.Resistor().left().label(part(M, 'R3', '100R'))
    d += elm.Label().label(G('HTR_PWM'), loc='left')

def b_relay(d):
    d += elm.Label().label('+24V', loc='left')
    d += elm.Switch(action='open').right().label('J3: KSD301 85 °C\nnormally closed (off board)')
    d += elm.Dot(); d += elm.Label().label('TSTAT_OUT', loc='top'); d.push()
    d += elm.Line().right(4.5); d += elm.Diode().down().reverse().label(part(M, 'D1', '1N4007'), loc='bottom')
    d += elm.Line().left(4.5)
    d.pop(); d += elm.Inductor2().down().label(part(M, 'K1', 'G5LE-1A4 DC24') + ' coil', loc='bottom')
    d += elm.Dot(); d += elm.Label().label('COIL_LO', loc='left')
    q = elm.BjtNpn(circle=True).anchor('collector').label(part(M, 'Q2', '2N3904'), loc='right'); d += q
    d += elm.Ground().at(q.emitter)
    d += elm.Line().at(q.base).left(2.5); d += elm.Dot(); d.push()
    d += elm.Resistor().down().label(part(M, 'R2', '10k'), loc='bottom'); d += elm.Ground()
    d.pop(); d += elm.Resistor().left().label(part(M, 'R1', '4k7'))
    d += elm.Label().label(G('RELAY_EN'), loc='left')

def b_fan_supply(d):
    d += elm.Label().label('+24V', loc='left')
    d += elm.Fuse().right().label(part(M, 'F3', '0.5A PTC'))
    d += elm.Line().right(1); d += elm.Label().label('FAN_24V → J4 pin 2\n(J4 pin 1 GND)', loc='right')

def b_fan_pwm(d):
    q = elm.BjtNpn(circle=True).label(part(M, 'Q3', '2N3904'), loc='right'); d += q
    d += elm.Line().at(q.collector).up(0.5); d += elm.Label().label('FAN_OC → J4 pin 4 (fan pulls it up)', loc='top')
    d += elm.Ground().at(q.emitter)
    d += elm.Line().at(q.base).left(2.5); d += elm.Dot(); d.push()
    d += elm.Resistor().down().label(part(M, 'R8', '10k'), loc='bottom'); d += elm.Ground()
    d.pop(); d += elm.Resistor().left().label(part(M, 'R7', '4k7'))
    d += elm.Label().label(G('FAN_PWM'), loc='left')

def b_fan_tach(d):
    d += elm.Label().label('TACH_RAW\nJ4 pin 3', loc='left')
    d += elm.Line().right(1); d += elm.Dot(); d.push()
    d += elm.Resistor().up().label(part(M, 'R5', '10k'), loc='bottom'); d += elm.Vdd().label('+3V3')
    d.pop(); d += elm.Resistor().right().label(part(M, 'R6', '1k'))
    d += elm.Dot(); d.push()
    d += elm.Capacitor().down().label(part(M, 'C2', '10nF'), loc='bottom'); d += elm.Ground()
    d.pop(); d += elm.Line().right(1); d += elm.Label().label(G('FAN_TACH'), loc='right')

def b_5v(d):
    d += elm.Label().label('+5V from the buck\n(J5 pin 3; pin 1 = +24V out)', loc='left')
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    d += elm.Schottky().right().label(part(M, 'D2', '1N5819'))
    d += elm.Dot(); d.push()
    d += elm.Capacitor().down().label(part(M, 'C7', '100nF'), loc='bottom'); d += elm.Ground()
    d.pop(); d += elm.Line().right(1); d += elm.Label().label('ESP_5V → DevKit 5V pin\n(blocks USB back-feed)', loc='right')

def b_led_feed(d):
    d += elm.Label().label('+5V', loc='left')
    d += elm.Fuse().right().label(part(M, 'F2', '3A PTC'))
    d += elm.Line().right(1); d += elm.Label().label('LED_5V → J6 → front J6', loc='right')

def b_pwr_led(d):
    d += elm.Label().label('+5V', loc='top')
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    d += elm.Vdd().label('+3V3')
    d += elm.Resistor().down().label(part(M, 'R14', '10k 1%'), loc='bottom')
    d += elm.Dot(); d.push()
    d += elm.Line().right(1.5); d += elm.Label().label(G('NTC') + ' (ADC1)', loc='right')
    d.pop(); d.push()
    d += elm.Line().left(2); d += elm.Capacitor().down().label(part(M, 'C4', '100nF'), loc='bottom'); d += elm.Ground()
    d.pop(); d += elm.Thermistor().down().label('J9: 10k NTC\nat the duct', loc='bottom'); d += elm.Ground()

def b_reed(d):
    d += elm.Vdd().label('+3V3')
    d += elm.Resistor().down().label(part(M, 'R15', '10k'), loc='bottom')
    d += elm.Dot(); d.push()
    d += elm.Line().right(1.5); d += elm.Label().label(G('REED') + '\n(switch: front J5, ribbon 18)', loc='right')
    d.pop(); d += elm.Capacitor().down().label(part(M, 'C5', '100nF'), loc='bottom'); d += elm.Ground()

def b_decouple(d):
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                     elm.IcPin(name='GND', side='bot', pin='7')],
               size=(3, 2.5), label=part(F, 'U1', '74AHCT125'))
    d += u
    d += elm.Line().at(u['1A']).left(1); d += elm.Label().label('LED_DIN\n(ribbon 12)', loc='left')
    d += elm.Line().at(u['1OE']).left(0.5); d += elm.Ground()
    d += elm.Line().at(u.VCC).up(0.5); d += elm.Vdd().label('LED_5V')
    d += elm.Line().at(u.GND).down(0.5); d += elm.Ground()
    d += elm.Resistor().at(u['1Y']).right().label(part(F, 'R4', '330R'))
    d += elm.Label().label('LED_DO → J7 pin 2 (strip DIN)\nchannels 2-4 off: OE to LED_5V, A to GND', loc='right')

def b_front_caps(d):
    d += elm.Label().label('LED_5V', loc='top')
    d += elm.Capacitor(polar=True).down().label(part(F, 'C5', '1000uF 16V') + ' at J7', loc='bottom'); d += elm.Ground()
    d.move(5, 3); d += elm.Label().label('LED_5V', loc='top')
    d += elm.Capacitor().down().label(part(F, 'C4', '100nF') + ' at U1', loc='bottom'); d += elm.Ground()
    d.move(5, 3); d += elm.Label().label('+3V3', loc='top')
    d += elm.Capacitor().down().label(part(F, 'C6', '100nF'), loc='bottom'); d += elm.Ground()
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

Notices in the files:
models/filament-dry-cabinet/firmware/dry-cabinet.yaml:
SPDX-License-Identifier: MIT
